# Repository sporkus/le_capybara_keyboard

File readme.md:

Le Capybara Keyboard
----

Capacitive sensing (aka Topre) keyboard in Le Chiffre layout

## Status
Fully tested 

## Manufacturing
Plates have m2 threaded holes for securing the plate and switches to the PCB.  DIY tapping is not difficult if your plate manufacturer does not offer tapping services.

Recommended plate material is 1.2mm steel. Plate files are in the expected physical dimensions. No kerf adjustments have been applied. The dxf files have been used successfully with SendCutSend and LaserBoost. JLCPCB is not recommnded for the plates without further testing to adapt to their milling process.

- [PCB production files](./production/)
- [Plate files](./plate/)

## Assembly

EC housing from DESKEYS and KLC playground have been tested.

#### Parts needed
- 32 - 34: 1u EC housing + slider
- 0 - 2: 2u EC housing + slider
- 34 - 36: Rubber domes
- 34 - 36: Conical springs
- 16: m2 x 8mm screws

**Optional**
- Silencing rings
- EC 11 rotary encoder or 1 MX switch for the center button

## Misc
#### 3D assembly preview
* [online viewer](https://3dviewer.net/#model=https://github.com/sporkus/le_capybara_keyboard/blob/dev/documentation/le_capybara-3D.step)
* [step assembly](./documentation/le_capybara-3D.step)

#### PCB Renders

#### Interactive BoM
Download and open this [html](./documentation/le_capybara-ibom.html) locally

#### Schematic
[pdf](./documentation/le_capybara-schematic.pdf)

## Change log
- 2024-02-21: V1.0 release for group buy. Change mounting method to tapped plate for ease of assembly.

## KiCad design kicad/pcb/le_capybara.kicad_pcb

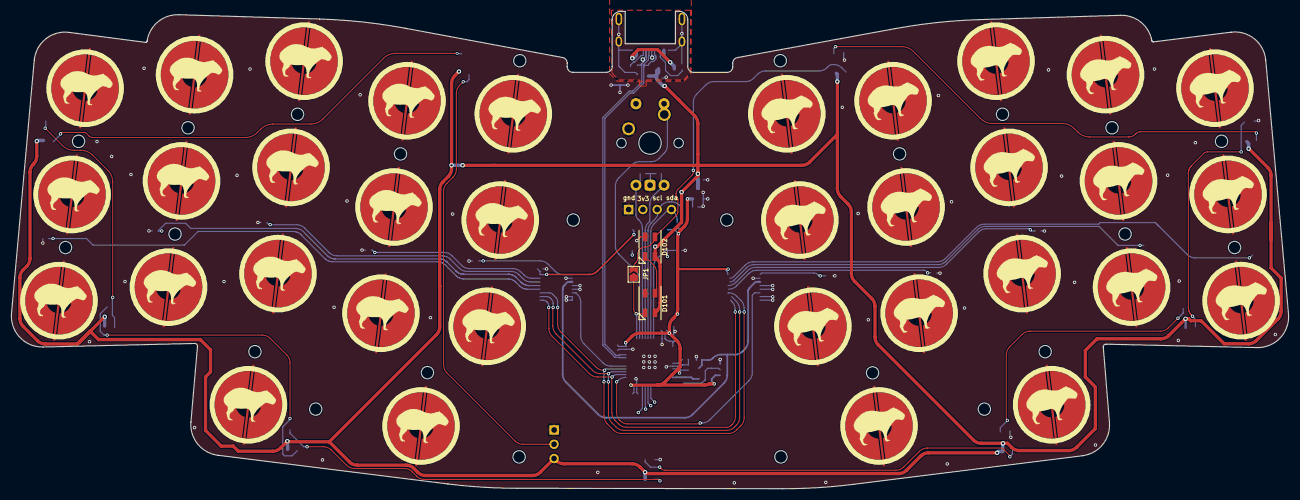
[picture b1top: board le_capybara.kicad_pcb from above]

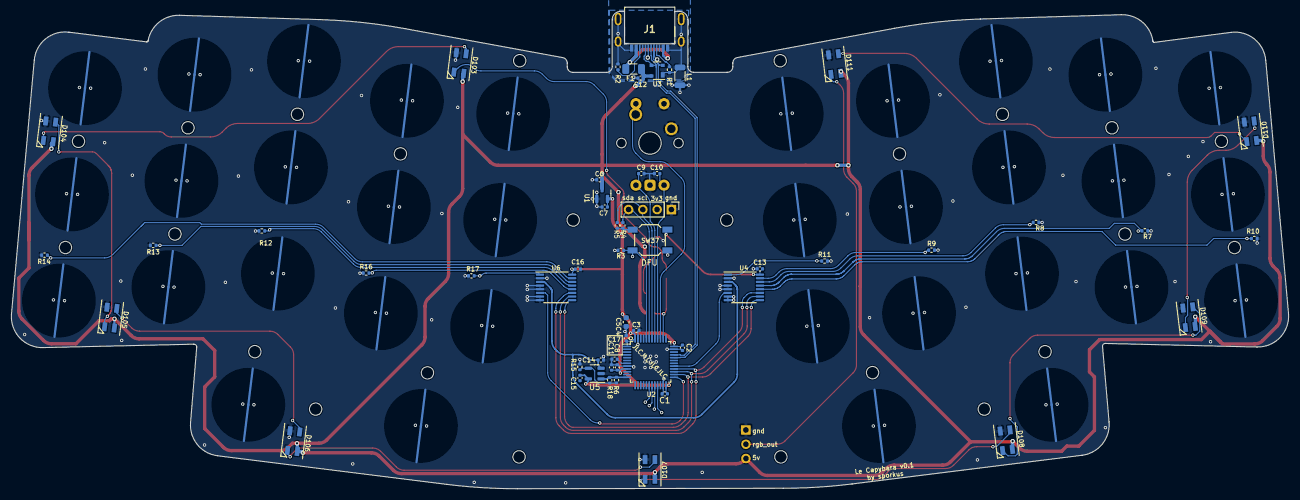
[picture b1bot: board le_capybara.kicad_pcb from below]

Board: 4 copper layers, 227.3 x 85.0 mm, 119 parts (55 on the bottom side), 49 nets.

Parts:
C1, C2, C3, C4, C9, C10, C12, C17: 100nF; C_0402_1005Metric
C5: 10uF; C_0603_1608Metric
C6, C7: 1uF; C_0402_1005Metric
C8, C13, C15, C16: 100n; C_0402_1005Metric
C11: 1u; C_0402_1005Metric
C14: 220pF NP0; C_0402_1005Metric
D101, D102, D103, D104, D105, D106, D107, D108, D109, D110, D111: SK6812MINI; LED_SK6812MINI_PLCC4_3.5x3.5mm_P1.75mm
F1: ASMD1206-150; Fuse_1206_3216Metric
H1, H2, H3, H4, H5, H6, H7, H8, H9, H10, H11, H12, H13, H14, H15, H16, H17, H18, H19, H20, H21, H22, H23, H24: MountingHole; MountingHole_2.2mm_M2_DIN965
J1: USB_C sink board 1.6mm; USB4510031A
J2: OLED I2C; PinHeader_1x04_P2.54mm_Vertical
J101: Conn_01x03_Female; PinSocket_1x03_P2.54mm_Vertical
JP1: Jumper_2_Open; SolderJumper-2_P1.3mm_Open_TrianglePad1.0x1.5mm
L1: 60R@100MHz; L_1206_3216Metric
R1, R2: 5.1k; R_0402_1005Metric
R3: 10k; R_0402_1005Metric
R4, R5: 4.7k; R_0402_1005Metric
R6, R7, R8, R9, R10, R11, R12, R13, R14, R16, R17: 100k; R_0402_1005Metric
R15: 1k; R_0402_1005Metric
R18: DNP; R_0402_1005Metric
SW1, SW2, SW3, SW4, SW5, SW6, SW7, SW8, SW9, SW10, SW11, SW12, SW13, SW14, SW15, SW16, SW17, SW18, SW19, SW20, SW21, SW22, SW23, SW24, SW25, SW26, SW27, SW28, SW29, SW30, SW31, SW32, SW33, SW34: EC_SW; capy_pad_1U_90deg
SW35: SW_Push; MX-Solderable-1U
SW36: Rotary_Encoder_Switch; ROT_Alps_EC11E-Switch
SW37: SKQGABE010; SW_SPST_SKQG_WithoutStem
U1: XC6206PxxxMR-Regulator_Linear; SOT-23
U2: STM32F072CBT6; LQFP-48_7x7mm_P0.5mm
U3: PRTR5V0U2X; SOT-143
U4, U6: 74HC4051; TSSOP-16_4.4x5mm_P0.65mm
U5: OPA354AIDBVR; SOT-23-5

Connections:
+3V3: C1.1, C2.1, C3.1, C4.1, C5.1, C7.2, C8.1, C11.1, C13.2, C15.2, C16.2, J2.2, R4.2, R5.2, SW37.1, U1.2 (VO), U2.1 (VBAT), U2.9 (VDDA), U2.24 (VDD), U2.36 (VDDIO2), U2.48 (VDD), U4.16 (VCC), U5.5 (V+), U6.16 (VCC)
+5V: C6.2, C12.1, D101.4 (VDD), D102.4 (VDD), D103.4 (VDD), D104.4 (VDD), D105.4 (VDD), D106.4 (VDD), D107.4 (VDD), D108.4 (VDD), D109.4 (VDD), D110.4 (VDD), D111.4 (VDD), F1.2, J101.3 (Pin_1), U1.3 (VI), U3.4 (VCC)
ADC: R6.1, R18.1, U2.12 (PA2), U5.1
AMUX_SEL_0: U2.28 (PB15), U4.11 (S0), U6.11 (S0)
AMUX_SEL_1: U2.27 (PB14), U4.10 (S1), U6.10 (S1)
AMUX_SEL_2: U2.26 (PB13), U4.9 (S2), U6.9 (S2)
APLEX_EN0: U2.29 (PA8), U4.6 (~E)
APLEX_EN1: U2.25 (PB12), U6.6 (~E)
APLEX_OUT: C14.1, U4.3 (A), U5.3 (+), U6.3 (A)
BOOT0: R3.1, SW37.2, U2.44 (BOOT0)
COL0: R10.1, SW1.2, SW11.2, SW21.2, U4.12 (A3)
COL1: R7.1, SW2.2, SW12.2, SW22.2, U4.13 (A0)
COL2: R8.1, SW3.2, SW13.2, SW23.2, SW31.2, U4.14 (A1)
COL3: R9.1, SW4.2, SW14.2, SW24.2, SW32.2, U4.15 (A2)
COL4: R11.1, SW5.2, SW15.2, SW25.2, U4.1 (A4)
COL5: R17.1, SW6.1, SW16.1, SW26.1, U6.1 (A4)
COL6: R16.1, SW7.1, SW17.1, SW27.1, SW33.1, U6.12 (A3)
COL7: R12.1, SW8.1, SW18.1, SW28.1, SW34.1, U6.13 (A0)
COL8: R13.1, SW9.1, SW19.1, SW29.1, U6.14 (A1)
COL9: R14.1, SW10.1, SW20.1, SW30.1, U6.15 (A2)
D_N: J1.A7 (D-), J1.B7 (D-), U2.32 (PA11), U3.2 (I/O1)
D_P: J1.A6 (D+), J1.B6 (D+), U2.33 (PA12), U3.3 (I/O2)
EncA: C10.1, SW36.A, U2.40 (PB4)
EncB: C9.1, SW36.B, U2.41 (PB5)
GND: C1.2, C2.2, C3.2, C4.2, C5.2, C6.1, C7.1, C8.2, C9.2, C10.2, C11.2, C12.2, C13.1, C14.2, C15.1, C16.1, C17.2, D101.2 (VSS), D102.2 (VSS), D103.2 (VSS), D104.2 (VSS), D105.2 (VSS), D106.2 (VSS), D107.2 (VSS), D108.2 (VSS), D109.2 (VSS), D110.2 (VSS), D111.2 (VSS), J1.A1 (GND), J1.A12 (GND), J1.S1 (SHIELD), J2.1, J101.1 (Pin_3), L1.1, L1.2, R1.1, R2.1, R3.2, R7.2, R8.2, R9.2, R10.2, R11.2, R12.2, R13.2, R14.2, R15.2, R16.2, R17.2, SW1.3 (SG), SW2.3 (SG), SW3.3 (SG), SW4.3 (SG), SW5.3 (SG), SW6.3 (SG), SW7.3 (SG), SW8.3 (SG), SW9.3 (SG), SW10.3 (SG), SW11.3 (SG), SW12.3 (SG), SW13.3 (SG), SW14.3 (SG), SW15.3 (SG), SW16.3 (SG), SW17.3 (SG), SW18.3 (SG), SW19.3 (SG), SW20.3 (SG), SW21.3 (SG), SW22.3 (SG), SW23.3 (SG), SW24.3 (SG), SW25.3 (SG), SW26.3 (SG), SW27.3 (SG), SW28.3 (SG), SW29.3 (SG), SW30.3 (SG), SW31.3 (SG), SW32.3 (SG), SW33.3 (SG), SW34.3 (SG), SW35.1, SW36.C, SW36.S2, U1.1 (GND), U2.8 (VSSA), U2.23 (VSS), U2.35 (VSS), U2.47 (VSS), U3.1 (GND), U4.2 (A6), U4.4 (A7), U4.5 (A5), U4.7 (VEE), U4.8 (GND), U5.2 (V-), U6.2 (A6), U6.4 (A7), U6.5 (A5), U6.7 (VEE), U6.8 (GND)
KNOB_SW: SW35.2, SW36.S1, U2.39 (PB3)
NRST: C17.1, U2.7 (NRST)
unnamed: D101.1 (DOUT), D102.3 (DIN)
unnamed: D102.1 (DOUT), D103.3 (DIN), JP1.2 (B)
unnamed: D103.1 (DOUT), D104.3 (DIN)
unnamed: D104.1 (DOUT), D105.3 (DIN)
unnamed: D105.1 (DOUT), D106.1 (DOUT)
unnamed: D106.3 (DIN), D107.1 (DOUT)
unnamed: D107.3 (DIN), D108.1 (DOUT)
unnamed: D108.3 (DIN), D109.1 (DOUT)
unnamed: D109.3 (DIN), D110.1 (DOUT)
unnamed: D110.3 (DIN), D111.1 (DOUT)
unnamed: D111.3 (DIN), J101.2
unnamed: J1.A5 (CC1), R1.2
unnamed: J1.B5 (CC2), R2.2
unnamed: R6.2, R15.1, R18.2, U5.4 (-)
RGB: D101.3 (DIN), JP1.1 (A), U2.38 (PA15)
ROW0: SW1.1, SW2.1, SW3.1, SW4.1, SW5.1, SW6.2, SW7.2, SW8.2, SW9.2, SW10.2, U2.18 (PB0)
ROW1: SW11.1, SW12.1, SW13.1, SW14.1, SW15.1, SW16.2, SW17.2, SW18.2, SW19.2, SW20.2, U2.19 (PB1)
ROW2: SW21.1, SW22.1, SW23.1, SW24.1, SW25.1, SW26.2, SW27.2, SW28.2, SW29.2, SW30.2, U2.20 (PB2)
ROW3: SW31.1, SW32.1, SW33.2, SW34.2, U2.21 (PB10)
SCL: J2.3, R5.1, U2.42 (PB6)
SDA: J2.4, R4.1, U2.43 (PB7)
VBUS: F1.1, J1.A4 (VBUS), J1.A9 (VBUS)

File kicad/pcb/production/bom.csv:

Designator,Footprint,Quantity,Value,LCSC Part #
"C1, C10, C12, C17, C2, C3, C4, C9",0402,8,100nF,C307331
C11,0402,1,1u,
"C13, C15, C16, C8",0402,4,100n,C307331
C14,0402,1,220pF NP0,C1530
C5,0603,1,10uF,
"C6, C7",0402,2,1uF,C52923
"D101, D102, D103, D104, D105, D106, D107, D108, D109, D110, D111",LED_SK6812MINI_PLCC4_3.5x3.5mm_P1.75mm,11,SK6812MINI,
F1,1206,1,ASMD1206-150,C135341
"H1, H10, H11, H12, H13, H14, H15, H16, H17, H18, H19, H2, H20, H21, H22, H23, H24, H3, H4, H5, H6, H7, H8, H9",MountingHole_2.2mm_M2_DIN965,24,MountingHole,
J1,USB4510031A,1,USB_C sink board 1.6mm,C2936201
J101,PinSocket_1x03_P2.54mm_Vertical,1,Conn_01x03_Female,
JP1,SolderJumper-2_P1.3mm_Open_TrianglePad1.0x1.5mm,1,Jumper_2_Open,
L1,1206,1,60R@100MHz,C33600
"R1, R2",0402,2,5.1k,
"R10, R11, R12, R13, R14, R16, R17, R6, R7, R8, R9",0402,11,100k,C25741
R15,0402,1,1k,C11702
R3,0402,1,10k,
"R4, R5",0402,2,4.7k,
"SW32, SW33",capy_pad_1U_90deg,2,EC_SW,
SW35,MX-Solderable-1U,1,SW_Push,
SW37,SW_SPST_SKQG_WithoutStem,1,SKQGABE010,C115351
U1,SOT-23,1,XC6206PxxxMR-Regulator_Linear,C5446
U2,LQFP-48_7x7mm_P0.5mm,1,STM32F072CBT6,
U3,SOT-143,1,PRTR5V0U2X,C2827688
"U4, U6",TSSOP-16_4.4x5mm_P0.65mm,2,74HC4051,C5645
U5,SOT-23-5,1,OPA354AIDBVR ,

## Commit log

2023-07-10 init
2023-07-20 try kibot
2023-07-20 [kibot]
2023-08-09 rerouted pcb
2023-08-09 clean up:
2023-08-23 getting ready for prototype
2023-08-23 Update config.kibot.yaml
    show components in render
2023-09-02 Major fixes after prototype order
    Fixed the following:
    - wrong RGB schematic, D106-D111 doesn't work
    - discharge pin from analog circuit was not connected
    - plate holes had the wrong diameter
2023-09-02 license
2023-09-11 schematic fix and plate tolerance fix
2023-09-11 add viewer link
2023-09-11 change plate thickness
2023-10-20 versioning pcb
2023-12-08 remove top mounting hole for chiffre+ compatibility
2024-02-03 adding three-thumbed plate
2024-02-06 add asymmetric plate
2024-02-06 fix 3-thumb plate kibot issue
2024-02-06 Making production plates
    - Change EC mounting hole size from 2.2mm clearance to 1.6mm for M2
    tapping
    - Reduce hole count for cost reduction
    - Add drilling/fabrication notes
2024-02-06 change kibot output
2024-02-06 reorganizing plate folder
2024-02-06 fix kibot pcb_print
2024-02-06 yaml fix
2024-02-06 Production plates - all versions
2024-02-07 fix 1.6mm hole footprint
2024-02-21 Clean up after prototyping
    - Doc update
    - remove uncessary files
    - remove two more mounting holes in the "chiffre gap" area
2024-02-21 remove notes
2024-02-22 Remove extra mounting holes from PCB and update version number.
2024-02-22 updated gerbers and doc
2024-03-02 remove extra notation
